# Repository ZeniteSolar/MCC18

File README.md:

# MCC18
Solar panel MPPT, cuk converter, with microcontroller 

# Procedimento de testes - MCC18

 - [Inspeção](#inspeção)
 - [Disgnostico Inicial](#diagnóstico-inicial)
 - [Diagnostico Preventivo](#diagnostico-preventivo)
 - [Teste Geral](#teste-geral)
    - [Entrada e saída de potencia](#entrada-e-saída-da-potência)
    - [Funcional](#funcional)
 - [Testes Individuais](#testes-individuais)
    - [Signals](#signals)
    - [MCC CAN Shield](#mcccanshield) 
 - [Driver](#driver)
    - [Esquematico](#esquemático)
    - [Reparos Obrigatorios](#reparos-obrigatórios)
    - [Verificando funcionamento](#verificando-se-está-funcionando)
    - [Correção de falhas](#correção-de-falhas)
        - [Se não houver sinal retangular na saída](#se-não-houver-sinal-retangular-na-saída)
        - [Se não houver +15V e -5V](#se-não-houver-15v-e--5v)
        - [Se não houver tensão em um dos barramentos de +15V ou -5V](#se-não-houver-tensão-em-um-dos-barramentos-de-15v-ou--5v)
        - [Se tem tensão no barramento, mas não tem sinal em gate e source](#se-tem-tensão-no-barramento-mas-não-tem-sinal-em-gate-e-source)

**Importante**: 
<span style="color:red">
NÃO TROCAR COMPONENTES ENTRE AS PLACAS, CADA MCC TEM SEU MCC_CAN_SHIELD, E CADA MCC_CAN_SHIELD TEM  SEU ATMEGA! 
SOMENTE REGRAVAR FIRMWARE EM ÚLTIMO CASO!
SEMPRE USAR LIMITE DE CORRENTE NAS FONTES!
SEMPRE LIMPAR EM BAIXO DO PLÁSTICO DOS CONECTORES BARRA_PINO!
</span>

Também Importante: Esse documento está escrito em ordem sequencial de testes, deve ser lido atentamente, pois um procedimento errado poderá causar danos permanentementes ao sistema, e as vezes difíceis de serem compreendidos.

## INSPEÇÃO
Antes de mais nada, limpeza com álcool e escova, mas especialmente em baixo das barras de pino, pois costumam acumular sujeira em baixo, entre o plástico preto e o cobre, eles podem ser levantados/retirados com uma pinça, fazendo uma alavanca, ou com um alicate universal.
Inspeção visual na placa inteira, especialmente por resíduos e manchas, que podem dar dica sobre onde pode existir problemas. Outro ponto de se observar são trilhas rompidas, componentes rachados ou com aspecto estranho.

## DIAGNÓSTICO INICIAL
Desconectar MCC_CAN_SHIELD, SIGNALS e DRIVER, bem como qualquer elemento externo a placa, como fontes de tensão.

Multímetro: entre B+ e P-, resistência dos indutores, na faixa de mOhms, se tiver alta impedância:
 - Um dos indutores em aberto
 - Shunt em aberto

Multímetro: entre P+ e P-, observar a carga do capacitor, um curto pode ser:
 - Capacitor do painel em curto
 - Mosfet em curto drain-source
 - Capacitor de acoplamento e diodo em curto
 - Capacitor de acoplamento e capacitor da bateria em curto

Multímetro: entre B+ e B-, observar a carga do capacitor, um curto pode ser:
 - Capacitor da bateria em curto
 - Diodo em curto
 - Capacitor de acoplamento em curto
 - Capacitor de acoplamento e capacitor do painel em curto

Multímetro: entre P+ e B-, observar a carga do capacitor de acoplamento, um curto pode ser:
 - Capacitor de acoplamento em curto
 - Diodo e Mosfet em curto

Multímetro: verificar se gate-source ou gate-drain não estão em curto.

## DIAGNOSTICO PREVENTIVO

IMPORTANTE, este diagnostico SOMENTE pode ser feito quando se tem certeza de que não houve um mal funcionamento do modulo, por exemplo o modulo ficou em repouso por um tempo e quer verificar o funcionamento. Este teste estima que o modulo não tem nenhuma falha destrutiva, se houver duvidas é recomendável fazer o diagnostico inicial e teste geral antes!!!.

ATENÇÃO! Nunca efetuar o teste sem resistor de carga entre B+ e B- se em algum momento houver a desconexão do mesmo pode danificar o modulo!

 - Ligar uma Fonte CAN a uma fonte de laboratorio com a tensão entre 18 e 30V, limitada em 0.05A e verificar o consumo, se a fonte limitar em corrente examinar o MCC_CAN_Shield está queimado, se não limitar em corrente esperar uns segundos e os leds deveriam piscar alternadamente (talvez passado um tempo um led fique fixo e outro desligado, não tem problema), se não o MCC_CAN_Shield está com problema.
 
 **(Sempre que for ligar uma placa no MCC desligar a fonte CAN (Se estiver usando uma fonte de laboratorio não desligue ela, desconecte o fio que alimenta o circuito é mais seguro))**

 - Com o MCC_CAN_Shield funcionando conecta-lo no MCC e aumentar o limite de corrente da fonte para 0.10A.
 - Conectar o driver e verificar o consumo, se limitar em corrente o driver está queimado, se não prosseguir.
 - Conectar a placa dos sensores, se limitar em corrente a placa está queimada, se não prosseguir.
 - **PASSO MUITO IMPORTANTE** Conectar o resistor de carga (valor máximo: 25R, recomendável: 20R, mínimo: 1R) entre B+ e B-
 - Ligar outra fonte (deve estar isolada) com a tensão em 0V e a corrente limitada a 0.05A entre +P e -P.
 - Medir a tensão de saída
 - Fazer uma rampa na fonte conectada em P+ e P- de 0V até 7V e de 0.05A até 1A (fazer devagar), enquanto faz a rampa a tensão de saída deveria aumentar se não aumentar e a fonte sempre ficar limitando em corrente, tem problema na parte de potencia, se a tensão de saída não aumentar e não houver consumo ou o driver ou a parte de potencia não funcionam
 - Se houve tensão na saída, a fonte de P+ e P- deveria ficar oscilando entre limite de corrente e limite de tensão e os LEDs da placa de controle deveriam estar alternando. Se não for o caso, desconectar o cabo RJ45 e conectar novamente, se mesmo assim depois de uns 30 segundos não ficar oscilando entre o limite de corrente e o limite de tensão, provavelmente algum sensor deve estar queimado.
 - Para diagnosticar o sensor conectar um Arduíno nos pinos de dados e na serial verificar se os valores medidos condizem com os que aparecem na fonte de P+ e P-.

## TESTE GERAL
Primeiro teste a ser realizado após limpeza e inspeção visual. Esse teste garante que as chaves e capacitores de potência estejam sem fuga de corrente para os níveis de tensão de trabalho nominal. Caso haja fuga de corrente, pode-se optar por aumentar o nível da corrente e localizar a fuga pela elevação de temperatura. 

<span style="color:red"> Importante: Obrigatório o uso de óculos de proteção.</span>

### Entrada e Saída da potência

Nesta etapa testamos o isolamento da placa, a capacidade dos capacitores de suportar a tensão, bem como dos indutores, trilhas, fusível e shunt de suportar a corrente.

 - Desenconectar o MCC_CAN_SHIELD, DRIVER e SIGNALS
 - Fazer uma rampa de tensão de 0 a 50V @ 100mA entre B+ e B-
 - Fazer uma rampa de tensão de 0 a 30V @ 100mA entre P+ e P-
 - Fazer uma rampa de tensão de 0 a 100V @ 100mA entre P+ e B-
 - Fazer uma rampa de corrente de 0 a 10A @ 1V entre B+ e P-

### Funcional
**Alimentação e CIs possivelmente vivos**

 - Remover o atmega do MCC_CAN_SHIELD
 - Conectar o MCC_CAN_SHIELD, ligar o cabo CAN, verificar baixo consumo
 - Medir tensão de 5V

**Geração de PWM e sinal de vida**

 - Conectar o atmega no MCC_CAN_SHIELD
 - Conectar o conector da rede CAN, verificar baixo consumo de corrente
 - Conectar USB/SERIAL para monitorar a serial, deve observar ‘Início com sucesso’
 - Deve haver o surgimento de sinal pwm no pino do conector onde o driver fica encaixado, assim como o aumento da variável de duty cycle pela serial. Talvez a verificação dos limites mínimos para funcionamento esteja ativa, nesse caso, precisa adicionar fontes na entrada e saída.
 - Remover fontes externas, conectar driver, verificar baixo consumo
 - <span style="color:red"> SEM ATERRAMENTO </span>, Medir Vgs, deve haver o mesmo sinal de pwm, de -5 a 15V @ 100kHz.

**Leitura de sinais de tensão**
 - Remover alimentação, conectar SIGNALS, MCC_CAN_SHIELD (com atmega)
 - Remover o DRIVER
 - Conectar USB/SERIAL para monitorar a serial
 - Fazer uma rampa de tensão de 0 a 30V @ 100mA entre P+ e P-:
    - Observar mudança na variável Vp
 - Zerar fonte de tensão:
    - Observar mudança na variável Vp
 - Fazer uma rampa de tensão de 0 a 50V @ 100mA entre B+ e B-:
    - Observar mudança na variável Vb
 - Zerar fonte de tensão:
    - Observar mudança na variável Vb

**MPPT e leitura de sinal de corrente**
 - Remover alimentação, conectar SIGNALS, MCC_CAN_SHIELD (com atmega), e DRIVER
 - Conectar USB/SERIAL para monitorar a serial
 - Resistência de carga no B+ e B-, pode ser na faixa de 100 Ohms
 - Fazer uma rampa de corrente de 1A @ 10V entre P+ e P-:
    -  <span style="color:red"> CUIDADO: </span> tensão na saída não deve ultrapassar 50V, se a carga for desconectada, capacitores podem explodir e sensor de corrente queimar.
 - observar busca pelo ponto de máxima potência
 - observar mudança na variável Ip

**MPPT com potência**
 - Ainda sem dissipador e com o mesmo setup anterior, reduzir a resistência e aumentar a tensão e corrente na entrada até 5A na entrada
 - Montar dissipador, e com o mesmo setup, chegar até 8A na entrada.

### TESTES INDIVIDUAIS
A SER REALIZADO CASO FALHE EM ALGUM TESTE GERAL.

#### SIGNALS

 - Alimentação:
    - Alimentar placa com 5V pela barra de pinos
    - Injetar sinal de tensão em cada pino de entrada de sinal da placa e verificar se a tensão nos pinos de saída.
 - Sensores:
    - Remover Atmega
    - Alimentar a placa com o conector do CAN
    - Botar sinal em cada pino do conector de ADC da placa e verificar se a tensão no MCU está correta

#### MCC_CAN_SHIELD

 - Alimentação:
    - Remover atmega
    - Alimentar a placa com o conector do CAN
    - Verificar baixo consumo de corrente
    - Verificar tensão de 5V
 - Sensores:
    - Remover Atmega
    - Alimentar a placa com o conector do CAN
    - Injetar sinal de tensão em cada pino do conector de ADC da placa e verificar se a tensão no MCU está correta
 - Atmega328:
    - Verificar pinos de alimentação do atmega (todos abaixo de 5V
    - Colocar atmega
    - Alimentar a placa com o conector do CAN
    - Verificar clock e reset do atmega
 - CAN:
    - Colocar atmega
    - Alimentar a placa com o conector do CAN
    - Verificar clock do MCP2515
    - Verificar clock na SPI
    - Verificar RX (entre MCP2515 e MCP2551), deve ter alguma coisa
    - Verificar TX (não deve ter sinal)
    - Verificar CAN_H e CAN_L, devem ter sinal se tiver sinal no RX ou TX
 - Funcionamento:
    - Colocar Atmega
    - Alimentar a placa com o conector do CAN
    - Verificar baixo consumo de corrente
    - Conectar na serial e ler as mensagens

### DRIVER

Procedimento de Reparo do Driver Isolado INEP
IMPORTANTE
<span style="color:red"> Para testar o driver é muito importante que todos os equipamentos estejam isolados com transformador isolador, já que ao ser um driver isolado qualquer tensão aplicada pela rede pode acabar queimando os componentes do mesmo.
Para reduzir riscos de ESD é importante colocar um resistor de alto valor entre o gnd e o source do Mosfet.
</span>

### ESQUEMÁTICO:

https://drive.google.com/drive/u/0/folders/0B_EOV_z-bdXUR3FXRHJyZm9FUkE?resourcekey=0-0dKXDxxFrtL1GblLArqhaQ

**Pinagem:**

<span style="color:red">Muito cuidado que este driver pode ser soldado nos dois sentidos sempre verificar onde está a bobina</span>

### Esquemático teste:

#### Reparos obrigatórios:
 
 - Trocar R80 para um resistor de 72 ohms
 - Trocar C28 por um capacitor de 1nF
 - Trocar RS01 e R301 por resistores de 220R

#### Verificando se está funcionando:

 - Antes de tudo fazer inspeção visual se todos os componentes estão nos seus devidos lugares 
 - Conectar o driver em uma protoboard e NÃO ESQUECER DE USAR TODOS OS EQUIPAMENTOS ISOLADOS E TER MUITO CUIDADO COM AS REFERENCIAS.
 - Conectar os dois resistores do esquemático e Colocar uma fonte limitada a 0.1A de 12V entre +12V e gnd (esquemático) e verificar o consumo de corrente, se está próximo aos (tem que medir) pode prosseguir com o teste se não ir para a etapa de correção de falhas.

 - Colocar um gerador de funções com 2.5V de amplitude e 2.5V de offset em 100khz e sinal retangular entre PWM e GND (não esquecer de conectar os dois GNDs) (é normal aumentar levemente o consumo)  e com um osciloscópio verificar se tem um sinal retangular entre gate e source de 100khz e Vmax de +15 e Vmin de  -5V. Se sim o driver pode ser testado em um controlador de carga. Se não vai ter que ir para a etapa de correção de falhas. 

#### Correção de falhas:
- Comportamentos:
#### Se não houver sinal retangular na saída
 - Verificar se tem +15V com a ponteira comum do multímetro no pino 4 do indutor e a vermelha no catodo do D300(localizado na proxima imagem)
 - Verificar se tem -5V com a ponteira comum do multímetro no pino 4 do indutor e a vermelha no anodo do D302(localizado na próxima imagem)

##### Se não houver +15V e -5V:
- Desconectar R80
 aplicar 12V em +12V e em GND (esquemático), colocar o osciloscopio com a referencia em GND e a ponteira no retângulo rosa da próxima imagem(pino 3 do 555 ou em R80) deveria ter uma sinal retangular de 250khz) se não houver o problema está no circuito do 555

 - Se houver sinal retangular o circuito do 555 está correto
 - Medir com o multímetro em tensão de junção (diodo) com a ponteira preta no pino 7 ou 8 de Q1 e com a vermelha no pino 1 deveria ter aproximadamente 0.7V, se estiver em 0 ou em circuito aberto significa que o Q1 está queimado,

 - Medir com o multimetro em tensão de junção (diodo) com a ponteira preta no pino 3 de Q1 e com a vermelha no pino 5 ou 6 deveria ter aproximadamente 0.7V, se estiver em 0 ou em circuito aberto significa que o Q1 está queimado, 

 - logo passar para as verificações do caso de Se não houver tensão em um dos barramentos de +15V ou -5V
 - Se nenhum desses procedimentos solucionarem , trocar Q1 (não esquecer de conectar R80) e verificar se volta a ter tensão em +15 e -5 
 
##### Se não houver tensão em um dos barramentos de +15V ou -5V
 - Medir com o multímetro em tensão de junção (diodo) e verificar se D300 e D302 estão funcionando corretamente, se não trocar
 - Medir com o multímetro em escala de ohms, entre o barramento (+15V e -5V) e GND, se houver curto em um unico barramento provavelmente seja C300, C42, C36, C38 para +15V em curto, C301, C37, C39, C43 para -5V em curto. 
 - Medir em tensão de junção (diodo) entre -5V (vermelha) e +15V (preta) deveria estar próximo dos 0.7V se não estiver DZ01 está com falha.
 - Medir entre o pino 5 e 2 da bobina com o multímetro em ohms, deveria estar proximo dos 0ohms, se estiver em circuito aberto significa que a bobina está mal soldada ou com enrolamento cortado.

##### Se tem tensão no barramento, mas não tem sinal em gate e source
 - Medir com o multímetro em tensão de junção entre os pinos 2 e 3 do U300, deveria ter aproximadamente 1.2V se não tem provavelmente U300 está queimado.

 - Medir entre o pino 6 ou 7 do U300 e o source do driver, com o multímetro em ohms, deveria ter aproximadamente 4.7k, se não tiver provavelmente DZ301 ou DZ302 estão queimados, ou também R303 ou R302 ou R300.
 - Com uma fonte limitada a 0.03A, com 20V conectar o positivo em +15V (catodo D300) e o negativo em -5V (anodo do D302), colocar um gerador de funções com sinal retangular offset de 2.5V, amplitude de 2.5V e frequencia de 100khz entre pwm e GND e um resistor de 10k entre GND e -5V. Medir com osciloscópio com a referencia no GND da fonte e com a ponteira no pino 6 ou 7 do U300, deveria ter um sinal retangular de 0 a 20V, se não houver ou se a fonte limitar provavelmente U300 está queimado, se houver testar trocando Q1 e ver se o driver funciona, se não provavelmente o driver está possuído, melhor ir para o proximo

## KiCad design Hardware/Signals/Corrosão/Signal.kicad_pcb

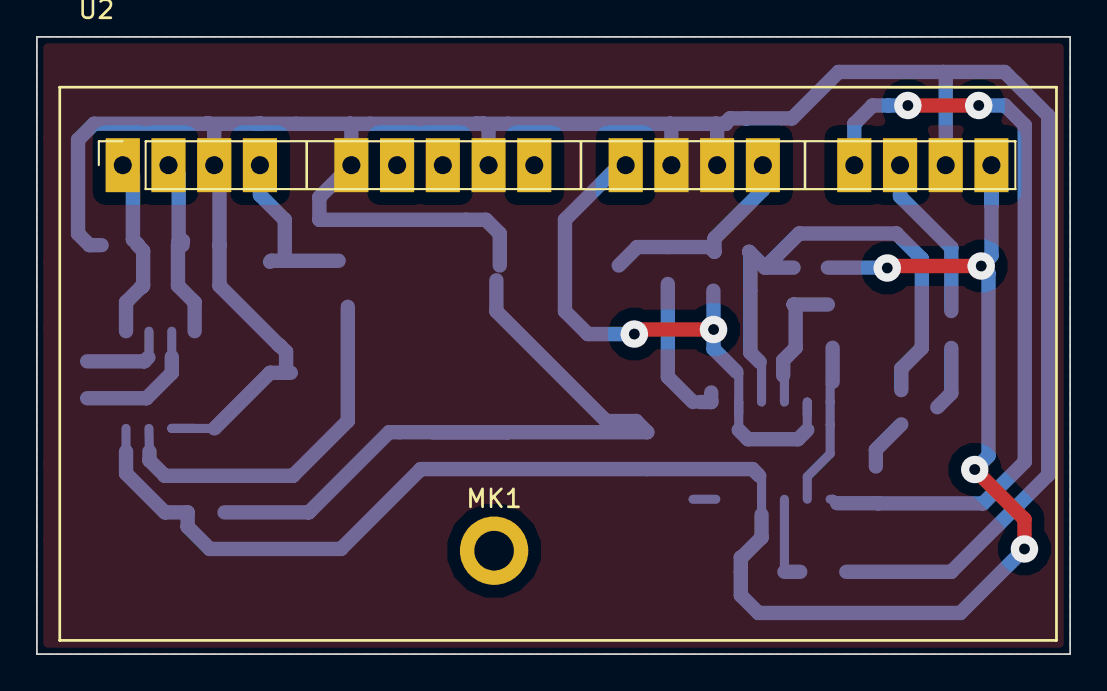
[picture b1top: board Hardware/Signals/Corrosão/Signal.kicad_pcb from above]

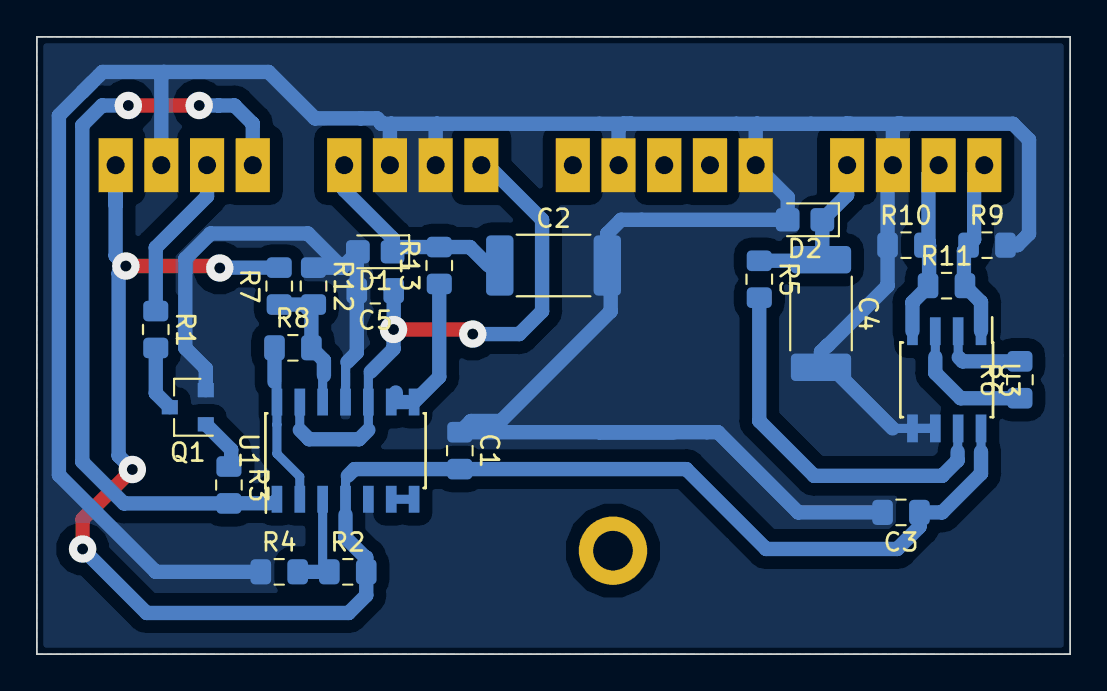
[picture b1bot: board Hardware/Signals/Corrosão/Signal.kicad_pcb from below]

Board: 2 copper layers, 57.4 x 34.3 mm, 25 parts (23 on the bottom side), 19 nets.

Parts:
C1: 100n; C_0805_2012Metric_Pad1.15x1.40mm_HandSolder
C2, C4: 10u; C_2512_6332Metric_Pad1.52x3.35mm_HandSolder
C3: 100nF; C_0805_2012Metric_Pad1.15x1.40mm_HandSolder
C5: 1n; C_0805_2012Metric_Pad1.15x1.40mm_HandSolder
D1, D2: D_TVS; D_0805_2012Metric_Castellated
MK1: Mounting_Hole; MountingHole_2.2mm_M2_DIN965_Pad
Q1: Q_NPN_Darlington_BEC; SOT-23
R1: 100; R_0805_2012Metric_Pad1.15x1.40mm_HandSolder
R2: 100k; R_0805_2012Metric_Pad1.15x1.40mm_HandSolder
R3: 220; R_0805_2012Metric_Pad1.15x1.40mm_HandSolder
R4: 56k; R_0805_2012Metric_Pad1.15x1.40mm_HandSolder
R5, R13: 150; R_0805_2012Metric_Pad1.15x1.40mm_HandSolder
R6: 15k; R_0805_2012Metric_Pad1.15x1.40mm_HandSolder
R7, R9, R10: 10k; R_0805_2012Metric_Pad1.15x1.40mm_HandSolder
R8: 12k; R_0805_2012Metric_Pad1.15x1.40mm_HandSolder
R11: 8.2k; R_0805_2012Metric_Pad1.15x1.40mm_HandSolder
R12: 75k; R_0805_2012Metric_Pad1.15x1.40mm_HandSolder
U1: LM324; SOIC-14_3.9x8.7mm_P1.27mm
U2: Signals_MCC; SignalsBarrapinosGrande
U3: INA826_D_8; SOIC-8_3.9x4.9mm_P1.27mm

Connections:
+5VA: C1.2, C3.1, R2.2, R7.2, U1.4, U2.17, U3.8
/BatOVInterrupt: R3.2, U1.1, U2.14
/PWM: R1.1, U2.15
/Vbat: C2.1, D1.1, R13.2, U2.13
/Vbat_SIG_IN: C5.1, U1.10, U1.13, U2.10
/Vpanel: C4.1, D2.1, R5.1, U2.4
/Vpanel_Ref: R9.1, R11.2, U2.1, U3.1
/Vpanel_SIG: R10.2, R11.1, U2.2, U3.4
GNDA: C1.1, C2.2, C3.2, C4.2, C5.2, D1.2, D2.2, Q1.2, R4.1, R9.2, R10.1, R12.1, U1.5, U1.11, U2.3, U2.5, U2.8, U2.11, U2.12, U2.16, U3.5, U3.6
unnamed: Q1.1, R3.1
unnamed: Q1.3, R1.2
unnamed: R2.1, R4.2, U1.3
unnamed: R5.2, U3.7
unnamed: R6.1, U3.3
unnamed: R6.2, U3.2
unnamed: R8.1, U1.2, U1.14
unnamed: R7.1, R8.2, R12.2, U1.12
unnamed: R13.1, U1.8, U1.9
unnamed: U1.6, U1.7

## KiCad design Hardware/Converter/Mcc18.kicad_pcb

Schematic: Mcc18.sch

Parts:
C1: 1uF; C_2512_6332Metric_Pad1.52x3.35mm_HandSolder
C2, C5, C10: 10uF; C_0805_2012Metric_Pad1.15x1.40mm_HandSolder
C3, C4, C8, C9, C11, C16, C17: 100nF; C_0805_2012Metric_Pad1.15x1.40mm_HandSolder
Cc1, Cc2, Cc3, Cc4, Cc5, Cc6, Cc7, Cc8, Cc9, Cc10, Cc11, Cc12: 1uF 100V; C_1206_3216Metric_Pad1.42x1.75mm_HandSolder
Ci1, Ci2, Ci3: 4,7uF 50V; C_1206_3216Metric_Pad1.42x1.75mm_HandSolder
Co1, Co2, Co3, Co4, Co5: 2.2uF 100V; C_1206_3216Metric_Pad1.42x1.75mm_HandSolder
Cs12, Cs13, Cs14, Cs15: 100nF; C_1206_3216Metric_Pad1.42x1.75mm_HandSolder
D1: 80CPQ150PbF; TO-247-3_Horizontal_TabUp
Ds1, Ds2, Ds3, Ds4: BYD77; D_MELF_Handsoldering
F1: Fuse; Porta_Fusivel
HS1: Heatsink; hs10425
JP1, JP4: VBat-Sen; SolderJumper-2_P1.3mm_Open_Pad1.0x1.5mm
JP5: ON/OFF; TerminalBlock_bornier-2_P5.08mm
L1, L3: L_Small; SolderJumper-2_P1.3mm_Open_Pad1.0x1.5mm
L1/2, L2/2: L_Core_Iron_Small; Inductor_Nocoupled
MK1: Mounting_Hole; MountingHole_2.2mm_M2_Pad
Q1: IRFP4321PbF; TO-247-3_Horizontal_TabUp
R101, R102: 330KR; R_0805_2012Metric_Pad1.15x1.40mm_HandSolder; Tolerance 1%
R103, R110: 100; R_0805_2012Metric_Pad1.15x1.40mm_HandSolder; Tolerance 1%
R105: 47R; R_0805_2012Metric_Pad1.15x1.40mm_HandSolder; Tolerance 1%
Rg1: 10k; R_0805_2012Metric_Pad1.15x1.40mm_HandSolder
Rs2, Rs3, Rs4, Rs5: 100; R_2512_6332Metric_Pad1.52x3.35mm_HandSolder
Rshunt1: 1500uR; PML100HZPJV0L5
Screw1: -P; MountingHole_5mm_Pad
Screw2: +P; MountingHole_5mm_Pad
Screw3: -B; MountingHole_5mm_Pad
Screw4: +B; MountingHole_5mm_Pad
TP1, TP2, TP3, TP4, TP5, TP6, TP7, TP8, TP9, TP10, TP11, TP12, TP13: TP; TestPoint_Pad_D1.0mm
Tvs1, Tvs2, Tvs4: D_TVS_ALT; D_0805_2012Metric_Castellated
Tvs3: Tvs; D_0805_2012Metric_Castellated
U1: INA240; SOIC-8_3.9x4.9mm_P1.27mm
U2: DRIVER_(INEP); Driver_(INEP)
U3: LM7812_TO220; TO-220-3_Horizontal_TabDown
U4: Signals_MCC; SignalsBarrapinos
U5: ZCS; ZCS18

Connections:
+5V: C17.1, L1.2, U5.5
+5VA: C11.2, C16.1, L1.1, TP13.1, Tvs3.1, U1.6, U4.17
+12V: C4.1, C5.1, C8.1, L3.1, U3.3 (VO)
/+18V_OUT: C2.1, C3.1, U3.1 (VI), U5.1
/+B: Co1.2, Co2.2, Co3.2, Co4.2, Co5.2, L1/2.2, R103.1, Screw4.1
/+Vp: Cc1.1, Cc2.1, Cc3.1, Cc4.1, Cc5.1, Cc6.1, Cc7.1, Cc8.1, Cc9.1, Cc10.1, Cc11.1, Cc12.1, Ci1.2, Ci2.2, Ci3.2, Cs15.2, Ds3.1, Ds4.2, Q1.2 (D), R102.1, Rs4.2, Screw2.1, TP10.1
/-B: Cc1.2, Cc2.2, Cc3.2, Cc4.2, Cc5.2, Cc6.2, Cc7.2, Cc8.2, Cc9.2, Cc10.2, Cc11.2, Cc12.2, Co1.1, Co2.1, Co3.1, Co4.1, Co5.1, Cs13.1, D1.1, D1.3, Ds1.2, JP1.1, JP4.2, Rs2.2, Screw3.1, TP7.1
/-P_unfused: F1.2, Screw1.1
/-Vp: Ci1.1, Ci2.1, Ci3.1, L2/2.1, R101.1, Rshunt1.1, U1.8
/BatOVInterrupt: U4.14, U5.9
/Gate: Q1.1 (G), Rg1.1, TP12.1, U2.1
/INA240_OUT: R110.1, U1.5
/Ipanel_adc+: C1.1, R110.2, TP4.1, Tvs1.1, U5.32
/PWM: U2.6, U4.15, U5.15
/Rs-: F1.1, Rshunt1.2, U1.1
/Source: Cs12.1, Cs14.1, D1.2, Ds2.2, L1/2.1, L2/2.2, Q1.3 (S), Rg1.2, Rs3.2, Rs5.1, TP6.1, TP11.1, U2.2
/Vb_sen+: R103.2, R105.2, TP1.1, U4.10
/Vb_sen-: JP4.1, R105.1, TP2.1, U4.11
/Vbat_adc+: TP5.1, Tvs2.1, U4.13, U5.33
/Vp_sen+: R102.2, TP9.1, U4.2
/Vp_sen-: R101.2, TP8.1, U4.1
/Vpanel_adc+: TP3.1, Tvs4.2, U4.4, U5.31
GND: C2.2, C3.2, C4.2, C5.2, C8.2, C9.2, C10.2, C17.2, JP1.2, JP5.1, U2.4, U2.7, U3.2 (GND), U5.2, U5.3, U5.4, U5.6, U5.7, U5.8, U5.18
GNDA: C1.2, C11.1, C16.2, Tvs1.2, Tvs2.2, Tvs3.2, Tvs4.1, U1.2, U1.3, U1.4, U1.7, U4.3, U4.5, U4.12, U4.16, U5.37
unnamed: C9.1, C10.1, L3.2, U2.5
unnamed: Cs12.2, Rs2.1
unnamed: Cs13.2, Ds2.1, Ds3.2, Rs3.1
unnamed: Cs14.2, Ds1.1, Ds4.1, Rs4.1
unnamed: Cs15.1, Rs5.2
unnamed: JP5.2, U5.10

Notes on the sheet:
Driver Supply
Obseravaçoes para a placa definitiva
Verificar Snubber || Colocar Tvs no lugar || Ver qual o footprint dos capacitores || Ver se eu n caguei nada
Current Sensor
Capacitor Bank 12uF 100V
Capacitor Bank 11uF 100V
Arrumar footprint snubber

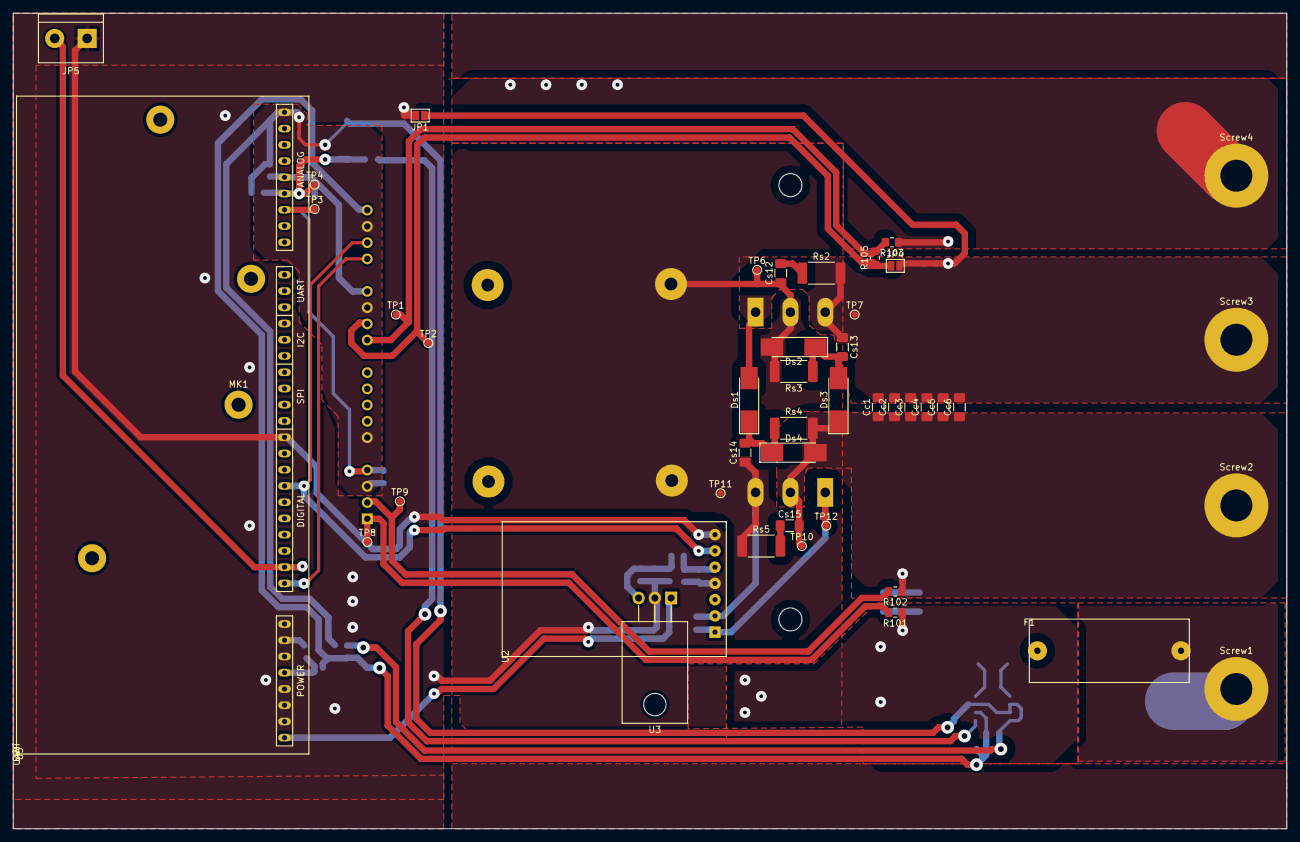
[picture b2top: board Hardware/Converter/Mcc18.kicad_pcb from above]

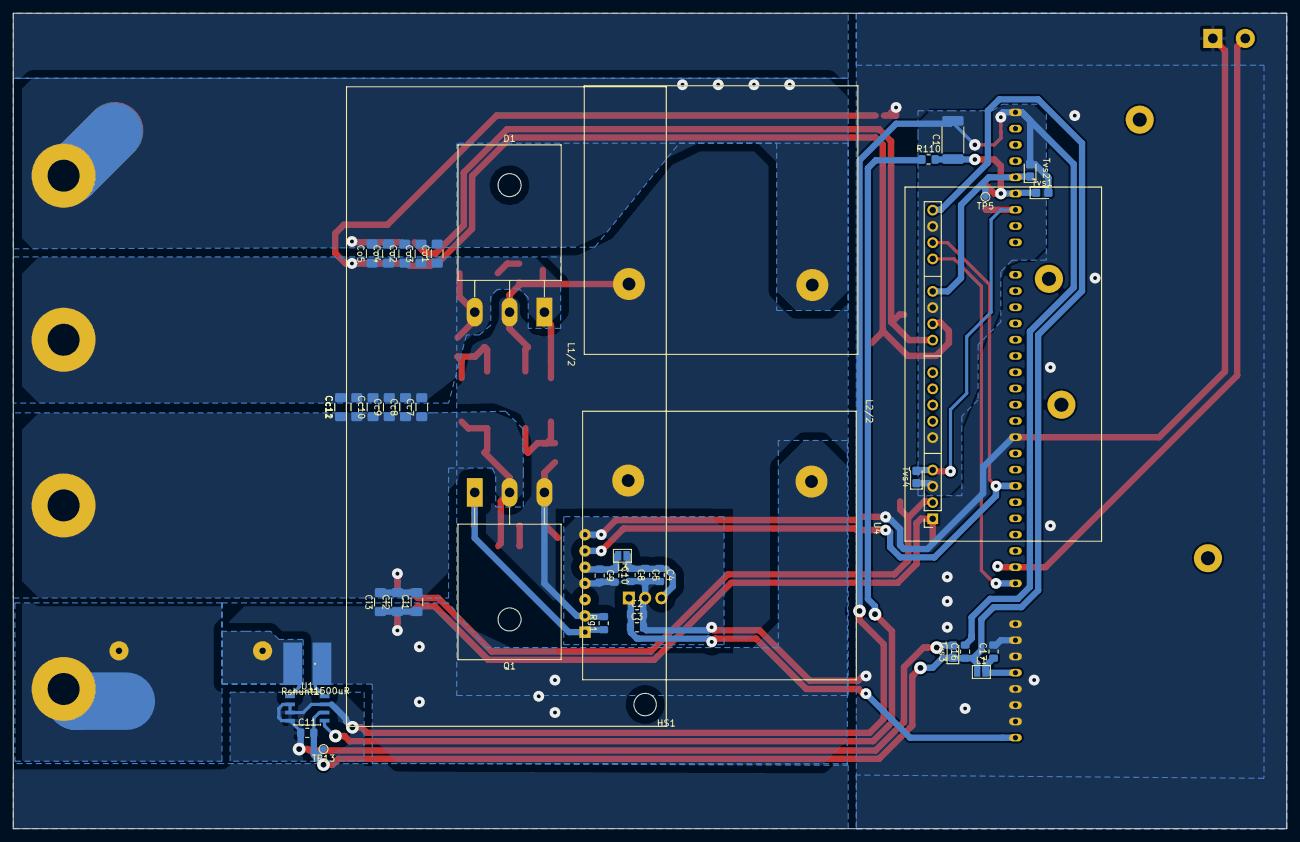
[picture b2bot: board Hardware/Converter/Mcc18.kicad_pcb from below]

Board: 2 copper layers, 199.1 x 127.5 mm, 88 parts (43 on the bottom side), 30 nets.

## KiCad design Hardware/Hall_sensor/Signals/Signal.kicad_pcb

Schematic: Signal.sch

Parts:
100k7: R13; R_0805_2012Metric_Pad1.29x1.40mm_HandSolder
100k8: R14; R_0805_2012Metric_Pad1.29x1.40mm_HandSolder
100k9: R15; R_0805_2012Metric_Pad1.29x1.40mm_HandSolder
C1, C2: C_Small; C_0805_2012Metric_Pad1.29x1.40mm_HandSolder
C7, C11: 100nF; C_0805_2012Metric_Pad1.29x1.40mm_HandSolder
C8, C9, C12, C13: 330p; C_0805_2012Metric_Pad1.29x1.40mm_HandSolder
C10, C14: 47p; C_0805_2012Metric_Pad1.29x1.40mm_HandSolder
D1: MMSZ5230BT1; D_SOD-123
MK1: Mounting_Hole; MountingHole_4mm_Pad_Via
Q1: Q_NPN_Darlington_BEC; SOT-23
R1, R2, R3, R4: R_US; R_0805_2012Metric_Pad1.29x1.40mm_HandSolder
R10, R11, R12, R16, R17, R18, R19, R20, R21, R22, R23, R24, R25, R26, R27, R28, R29: 100k; R_0805_2012Metric_Pad1.29x1.40mm_HandSolder
R31, R32, R33, R34, R35: ??; R_0805_2012Metric_Pad1.29x1.40mm_HandSolder
R_shunt1: 100k; R_0805_2012Metric_Pad1.29x1.40mm_HandSolder
U1: Signals_MCC; Signals
U2, U3, U4: LM324; SOIC-14_3.9x8.7mm_P1.27mm

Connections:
+5VA: C2.1, C7.2, C11.2, R1.2, U1.17, U2.4 (V+), U3.4 (V+)
/+3.9V: C1.1, D1.1, R1.1, U2.9 (-)
/BatOVInterrupt: R2.2, R3.1, U1.14, U2.8
/Ipanel: C8.1, U1.9, U3.8, U3.9 (-)
/Ipanel_Ref: R_shunt1.1, U1.7, U3.5 (+)
/Ipanel_SIG: R_shunt1.2, U1.6, U3.3 (+)
/PWM: R4.1, U1.15
/Vbat: U1.13, U2.6 (-), U2.7
/Vbat_SIG_IN: R34.2, U1.10
/Vpanel: C12.2, U1.4, U4.8, U4.9 (-)
/Vpanel_Ref: R32.1, R35.2, U1.1, U4.5 (+)
/Vpanel_SIG: R31.2, R35.1, U1.2, U4.3 (+)
GNDA: C1.2, C2.2, C7.1, C9.1, C10.1, C11.1, C13.1, C14.1, D1.2, Q1.2, R2.1, R19.2, R29.2, R31.1, R32.2, R33.2, U1.3, U1.5, U1.8, U1.11, U1.12, U1.16, U2.3 (+), U2.11 (V-), U2.12 (+), U3.11 (V-), U4.11 (V-)
unnamed: 100k7.1, R11.2, U3.14
unnamed: 100k7.2, 100k8.1, C9.2
unnamed: 100k8.2, 100k9.1, C8.2
unnamed: 100k9.2, C10.2, U3.10 (+)
unnamed: C12.1, R24.1, R25.2
unnamed: C13.2, R23.1, R24.2
unnamed: C14.2, R25.1, U4.10 (+)
unnamed: Q1.1, R3.2
unnamed: Q1.3, R4.2
unnamed: R10.1, R12.1, U3.7
unnamed: R10.2, R11.1, U3.13 (-)
unnamed: R12.2, R16.1, U3.6 (-)
unnamed: R16.2, R17.1, U3.2 (-)
unnamed: R17.2, R18.1, U3.1
unnamed: R18.2, R19.1, U3.12 (+)
unnamed: R20.1, R21.2, U4.13 (-)
unnamed: R20.2, R22.1, U4.7
unnamed: R21.1, R23.2, U4.14
unnamed: R22.2, R26.1, U4.6 (-)
unnamed: R26.2, R27.2, U4.2 (-)
unnamed: R27.1, R28.2, U4.1
unnamed: R28.1, R29.1, U4.12 (+)
unnamed: R33.1, R34.1, U2.5 (+), U2.10 (+)
unnamed: U2.1, U2.2 (-)
unnamed: U2.13 (-), U2.14

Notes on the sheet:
To bypass this instrumentation amplifier: 5 shorts 11 and 3 shorts 8.
3rd order Sallen-Key Low-Pass filter at 2728kHz
This signal is a current up to 12.5mA. 120 Ohms will produce 1.5V. It means that this overall bock needs to have a gain of 2 to produce 3V for the microcontroller.

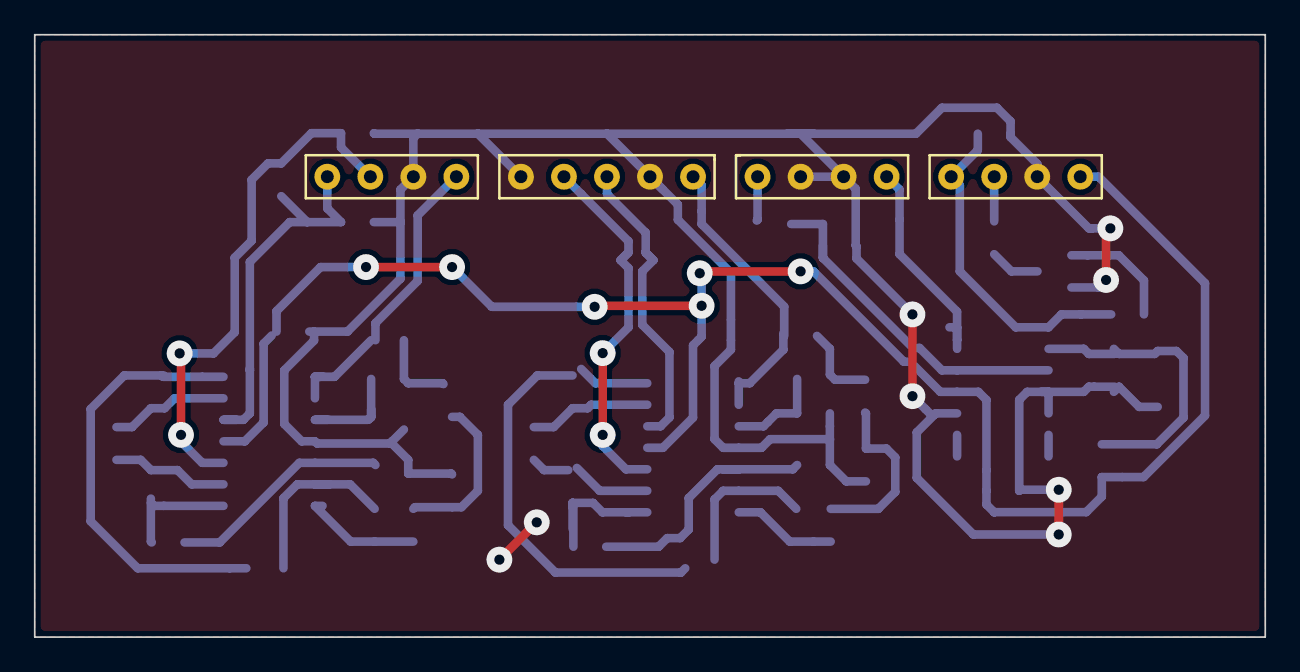
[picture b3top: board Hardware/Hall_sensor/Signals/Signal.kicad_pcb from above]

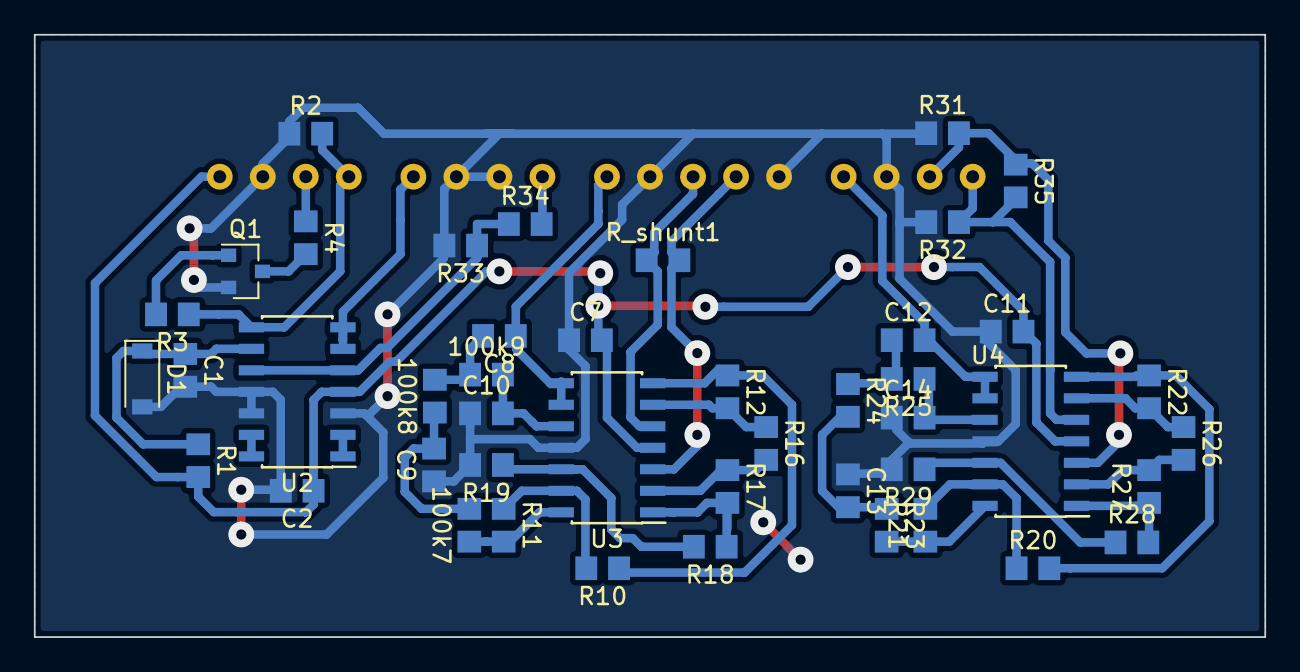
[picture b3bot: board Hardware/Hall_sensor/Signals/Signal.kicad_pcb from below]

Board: 2 copper layers, 72.6 x 35.6 mm, 46 parts (45 on the bottom side), 38 nets.

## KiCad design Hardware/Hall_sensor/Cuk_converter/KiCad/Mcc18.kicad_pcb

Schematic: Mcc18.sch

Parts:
C1, C3, C4, C6, C7, C8, C9: 100nF; C_0805_2012Metric_Pad1.29x1.40mm_HandSolder
C2, C5, C10: 10uF; C_0805_2012Metric_Pad1.29x1.40mm_HandSolder
Cc1, Cc2, Cc3, Cc4: 6.8uF; C_Rect_L29.0mm_W11.9mm_P27.50mm_MKT
Ci1, Ci2, Ci3: 4.7uF; C_Rect_L16.5mm_W9.2mm_P15.00mm_MKT
Co1, Co2, Co3: 4.7uF; C_Rect_L29.0mm_W11.9mm_P27.50mm_MKT
Cs1, Cs2, Cs3, Cs4: ??; C_1206_3216Metric_Pad1.39x1.80mm_HandSolder; Voltage 200V; Tolerance 10%
D1: 80CPQ150PbF; TO-247-3_Horizontal_TabUp
Ds1, Ds2: BYD77; D_MELF_Handsoldering
F1: Fuse; Porta_Fusivel
HS1: Heatsink; hs10425
L1: 50uH/50uH; NEE-42-20-DE
L2, L3: L_Small; L_0805_2012Metric_Pad1.29x1.40mm_HandSolder
Q1: IRFP4321PbF; TO-247-3_Horizontal_TabUp
R1: 10k; R_0805_2012Metric_Pad1.29x1.40mm_HandSolder
R101, R102, R103, R104: ??; R_0805_2012Metric_Pad1.29x1.40mm_HandSolder; Tolerance 1%
R105, R106: 0R; R_0805_2012Metric_Pad1.29x1.40mm_HandSolder; Tolerance 1%
Rs1, Rs4: ??; R_2512_6332Metric_Pad1.49x3.40mm_HandSolder; Tolerance 10%
Rs2, Rs3: ??; R_2512_6332Metric_Pad1.49x3.40mm_HandSolder
Screw1: -P; MountingHole_5mm_Pad
Screw2: +P; MountingHole_5mm_Pad
Screw3: -B; MountingHole_5mm_Pad
Screw4: +B; MountingHole_5mm_Pad
U1: LTSP_25-NP
U2: DRIVER_(INEP); Driver_(INEP)
U3: LM7812_TO220; TO-220-3_Horizontal_TabDown
U4: Signals_MCC; Signals
U5: ZCS; ZCS18

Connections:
+5V: C1.2, C7.1, L2.2, U1.7, U5.5
+5VA: C6.1, L2.1, U4.17
+12V: C4.1, C5.1, C8.1, L3.1, U3.3 (VO)
/+18V_OUT: C2.1, C3.1, U3.1 (VI), U5.1
/+B: Co1.2, Co2.2, Co3.2, L1.1, R103.1, Screw4.1
/+Ip: R105.1, U1.9
/+Vp: Cc1.1, Cc2.1, Cc3.1, Cc4.1, Ci1.1, Ci2.1, Ci3.1, Ds2.2, Q1.2 (D), R102.1, Rs2.2, Rs4.2, Screw2.1
/-B: Cc1.2, Cc2.2, Cc3.2, Cc4.2, Co1.1, Co2.1, Co3.1, D1.1, D1.3, Ds1.2, R104.1, Rs1.2, Rs3.2, Screw3.1
/-Vp: Ci1.2, Ci2.2, Ci3.2, F1.1, R101.1, U1.4
/BatOVInterrupt: U4.14, U5.9
/Gate: Q1.1 (G), R1.2, U2.1
/Ip_sen+: R105.2, U4.6
/Ip_sen-: R106.2, U4.7
/Ipanel_adc+: U4.9, U5.32
/PWM: U2.6, U4.15, U5.15
/Source: Cs1.2, Cs2.2, Cs3.2, Cs4.2, D1.2, L1.2, L1.4, Q1.3 (S), R1.1, U2.2
/Vb_sen+: R103.2, U4.10
/Vb_sen-: R104.2, U4.11
/Vbat_adc+: U4.13, U5.33
/Vp_sen+: R102.2, U4.2
/Vp_sen-: R101.2, U4.1
/Vpanel_adc+: U4.4, U5.31
GND: C1.1, C2.2, C3.2, C4.2, C5.2, C7.2, C8.2, C9.2, C10.2, R106.1, U1.8, U2.4, U2.7, U3.2 (GND), U5.3, U5.7, U5.18
GNDA: C6.2, U4.3, U4.5, U4.8, U4.12, U4.16, U5.37
unnamed: C9.1, C10.1, L3.2, U2.5
unnamed: Cs1.1, Rs1.1
unnamed: Cs2.1, Ds1.1, Rs2.1
unnamed: Cs3.1, Ds2.1, Rs3.1
unnamed: Cs4.1, Rs4.1
unnamed: F1.2, Screw1.1
unnamed: L1.3, U1.1, U1.2
unnamed: U1.3, U1.5, U1.6

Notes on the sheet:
In this config (2 turns) it senses up to 12.5A
CurrentSense
Driver Supply
Snubber
Obseravaçoes para a placa definitiva
Adicionar um divisor de tensão na medida de tensão da batria e painel , para que seja mais seguro

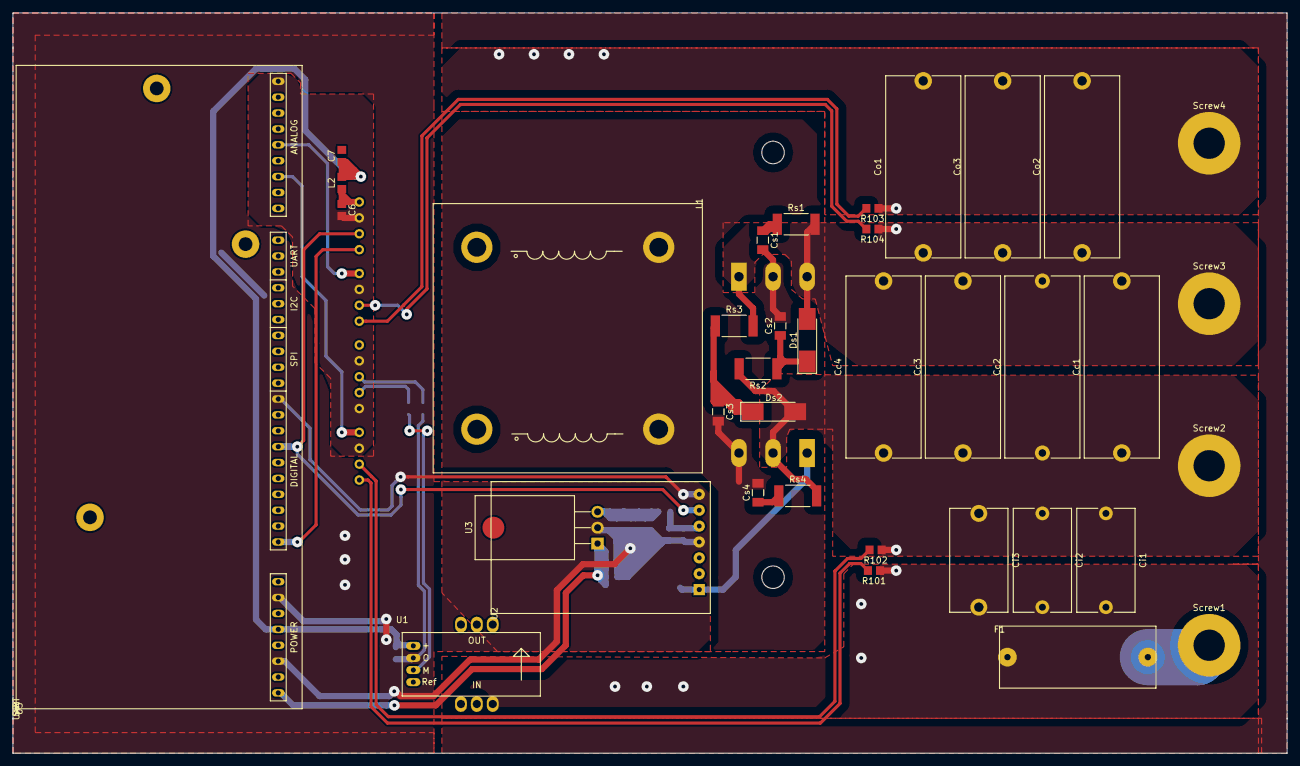
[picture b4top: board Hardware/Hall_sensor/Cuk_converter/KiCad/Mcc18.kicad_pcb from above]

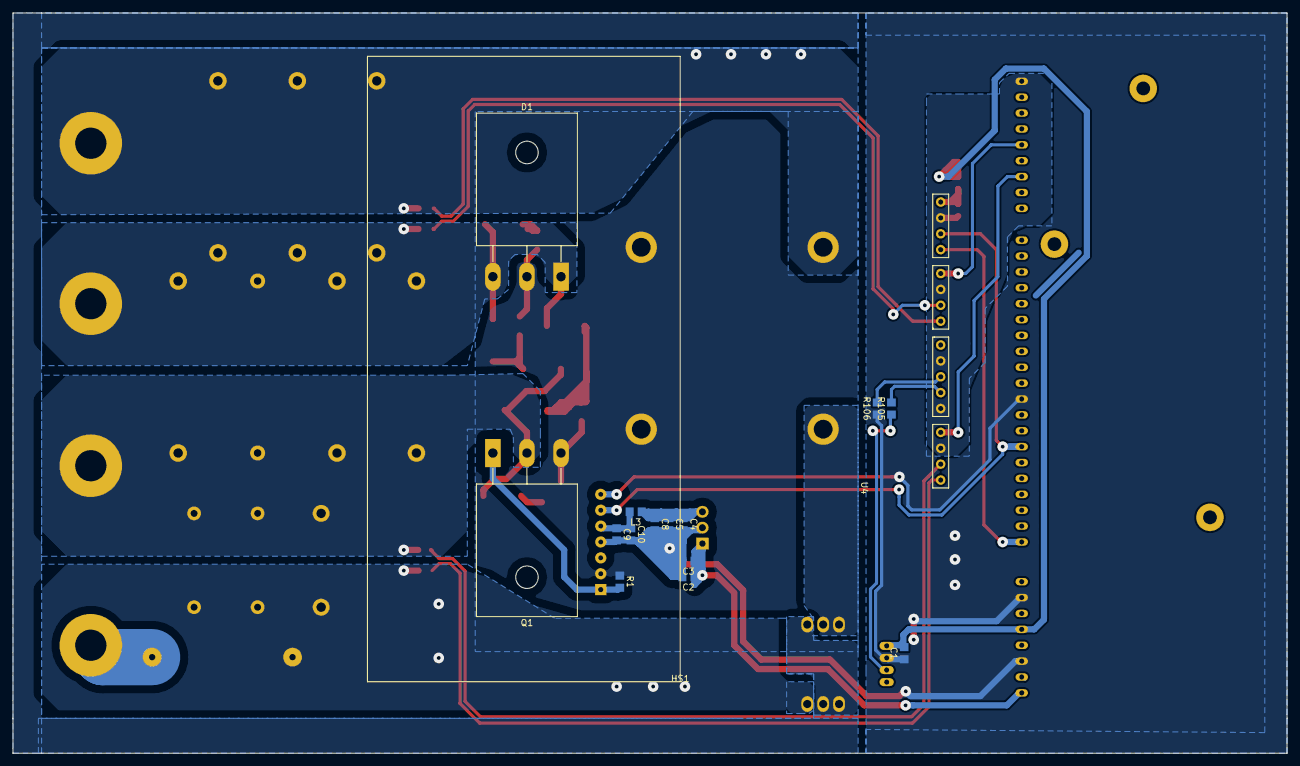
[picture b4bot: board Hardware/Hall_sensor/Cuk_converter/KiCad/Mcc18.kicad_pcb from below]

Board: 2 copper layers, 203.7 x 118.4 mm, 53 parts (16 on the bottom side), 32 nets.

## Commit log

2018-05-26 create signals directory
2018-05-26 snubber update
2018-05-26 Snubber finished
2018-05-26 Add cut board layer
2018-05-26 add a fill zone witout net
2018-05-27 Fixed errors
2018-05-28 created signals PCB
2018-05-28 created BOM of materials
2018-05-29 .wrl added, library link paths fixed
2018-05-30 cache-lib added to git (removed from gitignore)
2018-05-30 cache added
2018-05-30 maintain a zip file is unecessary.
2018-05-30 rework on snubber routing
2018-05-30 PCB Reworked
2018-05-30 Files to fabrication exported
2018-05-30 minor fixes and added IMG folder
2018-05-30 pads and traces of current sensor supply fixed
2018-05-30 minor fixes
2018-05-30 diff pairs locked
2018-05-30 some zones fix
2018-05-30 minor fixes. GERBERS updated
2018-05-30 Signals revisado. Foram reduzidos os jjumpers, GERBERS gerados e .wrl exportado.
2018-05-30 Atualizado 3D do signals para .wrl
2018-05-30 power trace optimized
2018-05-30 first try... Some problems because CAPS arn't smd
2018-05-30 Version done. Revision needed.
2018-05-31 created shunt sensor PCB
2018-05-31 ok. Now it is on 25~50mils grid.
2018-06-01 finished the first version
2018-06-01 fixed clearance
2018-06-01 fixed shunt tracks and added 3d images
2018-06-03 Added signals PCB Added signals PCB for shunt current sense
2018-06-03 Fixed voltage divider The old voltage divider isn't differential
2018-06-03 Added signals 3D in cuk PCB _Added signals 3D in signals component in MCCshunt Library._ _Added pin socket in the signals component_ _Added signals component in cuk converter PCB_ _Added MountingHole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
2018-06-03 Genereted fabrication files to the Shunt sensor _Generated signals GERBER_ _Generated signals drill_ _Generated signals 3D Images_ _Generated signals PDF_ _Generated Cuk converter GERBER_ _Generated 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
2018-06-03 Updated fabrication outputs _Updated shunt signals PDF schematic,PDF PCB, GERBER PCB,Drill PCB_ _Updated shunt cuk PDF schematic,PDF PCB, GERBER PCB,Drill PCB_ _Updated hall signals PDF schematic,PDF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
2018-06-03 generated drill map and report file
2018-06-03 shunt signals updated
2018-06-03 gerated PDF
2018-06-03 Modified Angled 3D IMG to Shunt cuk
2018-06-03 added 3D images
2018-06-04 Replaced all spaces to "_"
2018-06-04 fixed and created all Fabrication files
2018-06-04 created compressed Fabrication files
2018-06-05 crated new fill zones and minimized holes sizes
2018-06-06 Basic simulations with shunt added
2018-06-06 sensors fixed on simulation. Everything seems working fine
2018-06-06 Shunt_Cuk fixed _Switchs of the cuk fixed_ _Added isolation between the high voltage and the low voltage_
2018-06-07 Added trak between Shunt and Inductor
2018-06-07 Fixing the Hall_Cuk
2018-06-15 Copper Clearence fixed
2018-06-22 Added a script (matlab) to find the best E12 resitors to minimize gain error
2018-06-22 Added simulation (LTspice) for input voltage measurement.
2018-06-29 finalized shunt cuk
2018-07-18 initial firmware copied from MCC17, small changes to compile and upload for 328pb
2018-07-18 changed MISO and MOSI using software serial
2018-07-18 added pragma messages for included modules
2018-07-20 Chaned to compile atmega328pb
2018-07-20 unecessary file.
2018-07-20 SILENCE enabled
2018-07-20 modules interdependency fixed
2018-07-20 gitignore updated
2018-07-20 Status led changed to new pin and added a blink pattern to main loop if MACHINE_ON isnt defined.
2018-07-20 ADC setted to 5kHz, some other minor improvements.
2018-07-20 Comments added
2018-07-20 USART, WATCHDOG, PWM, ADC working. Now testing machine
2018-07-20 ADC readings tested, ifdefs 8bits fixed
2018-07-20 ADC tested: OK. Reading 1021 at 5V, 0 at 0V
2018-07-22 PWM changed to mode 14 to get better resolution for 100kHz.
2018-07-22 code organization
2018-07-22 added a print version for 32 bits unsigned
2018-07-30 Added precompiled PWM configurations. Tested -> OK
2018-08-22 wdt time changed to 4 seconds because 2 wasn't fine
2018-08-22 This is almost the firmware for MCC module
2018-08-22 Initialized de final version
2018-08-23 Added snubber and driver
2018-08-23 Finlized signals basic routing
2018-08-23 Added ADC tracks
2018-08-24 Some 3D added, power reworked to minimize stray inductances
2018-08-24 testing...
2018-08-24 adc_data_ready changed to machine_run instead task_running to ensure that moving average is rightly done
2018-08-24 adc_data_ready initialized in adc_init instead adc.h
2018-08-24 algorithm for zero power detection enhanced
2018-08-25 checks are now part of a decision tree centralized inside read_and_check_adcs(void)
2018-08-25 machine prints was causing clock conflict. Fixed
2018-08-25 remove duplicated F_CPU define
2018-08-25 Added fill zones
2018-08-26 various specific changes
2018-08-26 doc added
2018-08-30 Finalized first version PCB
2018-08-31 final adjusted for cnc.
2018-08-31 Fixed signals tracks
2019-04-18 gitignore from Firmware
2019-04-18 changes after Buzios
2019-08-30 resgate dos arquivos
2019-08-30 remoção do 3D da placa
2022-09-07 Simulate INEP driver and fix some components values
2022-09-15 DOC: Add test procedures and repair tutorial
2022-09-20 DOC: Add diagnostico preventivo

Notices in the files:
parts and their libraries:
Copyright 2016 Accelerated Designs. All rights reserved.
